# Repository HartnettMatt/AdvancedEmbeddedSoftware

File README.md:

# AdvancedEmbeddedSoftware
Matt's work in ECEN5713, Advanced Embedded Software

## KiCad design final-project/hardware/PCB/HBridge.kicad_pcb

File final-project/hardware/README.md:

# Final Project Hardware

Here is all of the hardware for the whiteboard wiper robot.

### Directory Structure:

hardware/ <br>
├── 3D_Printing # 3D Printing files and designs <br>
│ ├── *.FCStd # Part's Free CAD file, used for editing <br>
│ ├── *.stl # Part's STL export, imported into slicer <br>
│ └── *.gcode # Part's sliced file (specific to Matt's 3D printer, DO NOT USE ELSEWHERE) <br>
├── Spice # Circuit simulations<br>
│ ├── *.asc # Design's LTSpice file, used for editing <br>
│ ├── *.log # Design's log file <br>
│ └── *.raw # Design's raw file <br>
├── Docs # Important documentation<br>
│ ├── HCS04.pdf # Specifications for distance sensor <br>
│ ├── MJE200_D-1811381.pdf # Specifications for NPN <br>
│ └── MJE210_D-2316039.pdf # Specifications for PNP <br>
├── raspberryPiPinout.png # Pinout
image, [Source](https://www.raspberrypi.com/documentation/computers/raspberry-pi.html)<br>
└── README.md # Project documentation (this file) <br>

## Raspberry Pi Pinout:

## Important pins:

| RPi Pin | Label    | Net Name    | Connection         |
|---------|----------|-------------|--------------------|
| 4       | 5V Power | VCC         | Power cable red    |
| 6       | Ground   | GND         | Power cable black  |
| 10      | GPIO 15  | RM_1        | Right motor orange |
| 12      | GPIO 18  | RM_2        | Right motor green  |
| 16      | GPIO 23  | LM_1        | Left motor blue    |
| 18      | GPIO 24  | LM_2        | Left motor yellow  |
| 11      | GPIO 17  | HCSR04_TRIG | HCSR04 (TBD)       |
| 13      | GPIO 27  | HCSR04_ECHO | HCSR04 (TBD)       |

### Notes:

* ECHO pin of the HCS04 is connected to a 1k/2.2k voltage divider to convert from 5V to 3.3V (roughly)
* If motor mount v2:
    * Tighten tolerances around hex holes
    * Add 3rd mount point for PCB
    * Add indent for motor screws

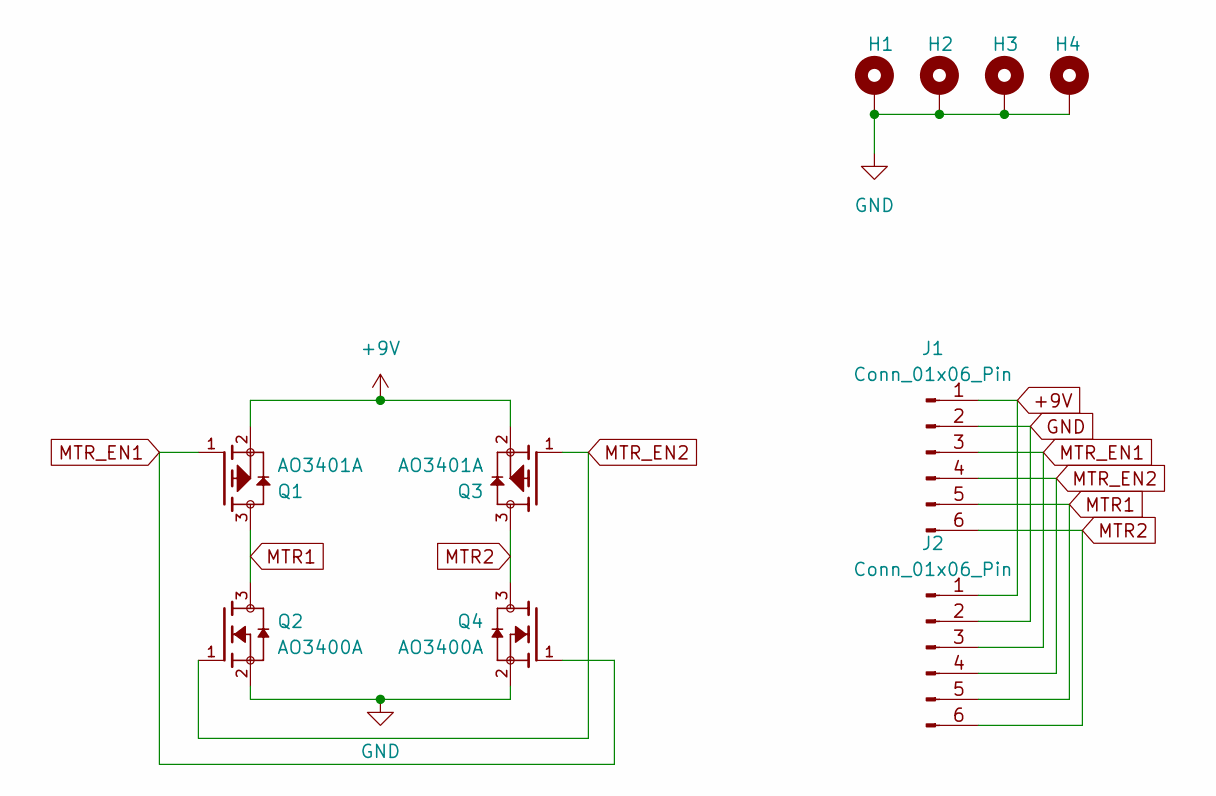
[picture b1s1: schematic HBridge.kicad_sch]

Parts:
H1, H2, H3, H4: MountingHole_Pad; MountingHole_3.2mm_M3_DIN965_Pad
J1, J2: Conn_01x06_Pin; PinHeader_1x06_P2.54mm_Vertical
Q1, Q3: AO3401A; PARTREV L
Q2, Q4: AO3400A; SOT95P280X125-3N; PARTREV L

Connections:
+9V: J1.1, J2.1, Q1.2, Q3.2
GND: H1.1, H2.1, H3.1, H4.1, J1.2, J2.2, Q2.2, Q4.2
MTR1: J1.5, J2.5, Q1.3, Q2.3
MTR2: J1.6, J2.6, Q3.3, Q4.3
MTR_EN1: J1.3, J2.3, Q1.1, Q4.1
MTR_EN2: J1.4, J2.4, Q2.1, Q3.1

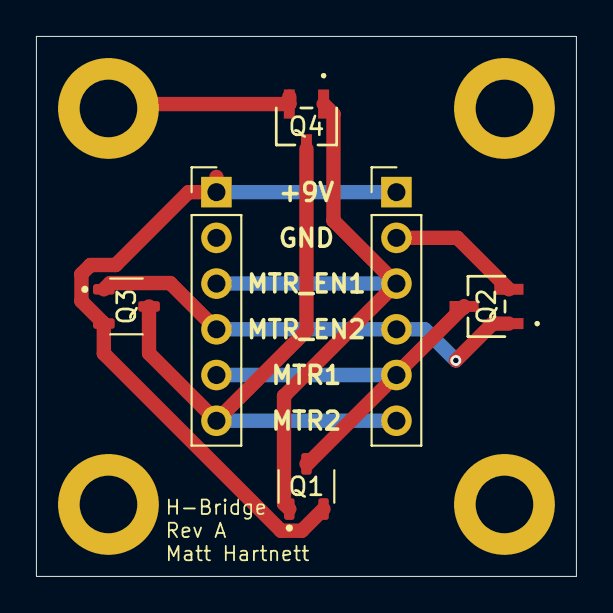
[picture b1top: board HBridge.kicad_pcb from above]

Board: 2 copper layers, 30.0 x 30.0 mm, 10 parts (0 on the bottom side), 6 nets.

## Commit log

2025-01-26 Completed assignment 1
2025-02-02 Added assignment 2
2025-04-05 Began work on final project
2025-04-08 Rev 1 of the motor mount
2025-04-08 Added gitignore, finished rev 2 of motor mount
2025-04-10 Designed H-bridge
2025-04-13 First attempt at GPIO test driver
2025-04-13 Updated H Bridge circuit sim
2025-04-13 Switched from - to _ in gpio_test file and folder names
2025-04-13 Updated from LIBGPIOD to LIBGPIOD2
2025-04-13 Updated gpio_test
2025-04-13 Reverted back to LIBGPIOD
2025-04-13 Trying libgpiod2 again
2025-04-13 Added API VERSION
2025-04-13 Added library version to makefile
2025-04-13 gpio test
2025-04-13 gpio test 2
2025-04-13 Designed and printed v1 of the motor mount platform
2025-04-13 gpio test 3
2025-04-13 gpio test 4
2025-04-13 gpio test 5
2025-04-14 Added a debug log and updated gpio_test
2025-04-14 GPIO test 6
2025-04-14 GPIO test 7
2025-04-14 Copied example libgpio
2025-04-14 Updated makefile based on professor's suggestions
2025-04-14 Changed from single GPIO toggle to full motor power on self test
2025-04-17 Added hardware docs and designed v1 of Raspberry Pi Platform
2025-04-17 Designed wheel adapter version 1
2025-04-17 Added todo list and formatted code better
2025-04-17 Re-organized hardware folder, added a lot of documentation
2025-04-17 Renamed driver README and wrote a hcsr04 port and test
2025-04-18 Redesigned RPi platform and wheel adapter
2025-04-18 Updated makefile
2025-04-18 Updated makefile again
2025-04-18 Updated makefile again again
2025-04-18 Fixed bugs in port code
2025-04-18 Added in delay functions
2025-04-18 Switched to event driven instead of polling
2025-04-18 Hopefully fixed post init stuck issue
2025-04-18 Testing something
2025-04-18 Changed CPU priority and forced single core
2025-04-18 Clamped values to be less than 1000us
2025-04-19 First attempt at full control loop
2025-04-19 Fixed some issues
2025-04-19 Fixed more issues
2025-04-19 Fixed more more issues
2025-04-19 Fixed dumb mistake
2025-04-19 Designed v1 of the battery holder
2025-04-19 Fixed thing?
2025-04-19 Added self testing into main loop
2025-04-19 Added more prints
2025-04-19 Added newlines
2025-04-19 Fixed dumb bug in motor
2025-04-19 Tidied up code and changed some constants
2025-04-19 Missed save of platform
2025-04-25 Designed v1 of the eraser holder
2025-04-28 Finished designing all prints, updated README
2025-05-23 Updated bottom platform and finished iteration 1 of hardware system
2025-05-23 Started a new wheel adapter for newer, smaller motors
2025-05-26 Finished making new wheel adapter that fits with new motors
2025-05-30 Finished H Bridge PCB design
2025-05-31 Made a lot of progress on the new main body of the updated robot
2025-05-31 PCB Backup update
2025-05-31 Battery Holder V3
2025-11-16 Continued work on whiteboard robot
2025-11-16 Removed manual assignment additions
